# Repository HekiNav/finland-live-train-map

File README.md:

# Finland live train map

The project consist of the physical pcb and case as well as the server that processes the information from the api and serves it to the ESP-32 to process. The physical project is a pcb with LEDs marking the route for intercity trains across Finland. There are two versions of the map. A more simplified version with just the routes visible. Then there is the more geografically correct version with the borders of Finland printed on the silkscreen. The LEDs mark the position of trains in real time so you can see at a glance where the trains are. The case makes it possible to wall mount the pcb or have it on your desk.

This project was made for Hack Club [Fallout](https://fallout.hackclub.com) by [NoseFa](https://github.com/NoseFa) and [Hekinav](https://github.com/HekiNav).

## Repository structure / table of contents

NOTE! All software has been moved to [another repo (HekiNav/ltm-firmware)](https://github.com/HekiNav/ltm-firmware)

**Each directory contains its own README file with more detailed information on the specific section. Basic information is provided here.**

### [`/pcb`](./pcb/README.md)
Contains KiCad design files
View interactive PCB design in [KiCanvas](https://kicanvas.org/?github=https%3A%2F%2Fgithub.com%2FHekinav%2FFinland-Live-Train-Map%2Ftree%2Fmain%2Fpcb)

### [`/design`](./design/README.md)
Contains Map Design ideas and plans as Inkscape SVGs

### [`/server`](https://github.com/HekiNav/ltm-firmware/tree/main/server/README.md)
Contains the NodeJS server that processes data from Fintraffic to amore usable format

### [`/firmware`](https://github.com/HekiNav/ltm-firmware/tree/main/firmware/README.md)
Contains the Platformio firmware for the ESP32C3

### [BuildGuide.md](BuildGuide.md)
Contains instructions for building the project.

## Why this exists

This project was made because we wanted to work on something together and Hack Club was running the Fallout event. Hekinav has built a similar type of project before for Helsinki. [The Helsinki Live Train map](https://github.com/HekiNav/helsinki-live-train-map) and we decided that making one of all the Trains in Finland would be cool. This project is meant to be something to look at and something cool to have in your space. Thats why we put so much effort in the silkscreen of the pcb and the placement of the LED's. We wanted it to be good to look at.

## BOM

The BOM for this project is pretty much just making buying the PCB and then 3d printing the case (we are self-printing so we didn't add this). You can see the JLCPCB formatted [BOM.csv](./pcb/jlcpcb/production_files/BOM-fin-ltm.csv). We have some more detailed information about how to order it. Here is also a table that just includes the price of the PCB and the assembly, shipping + customs for it.

|         Part          |   Total price   |                     Link                            |   Extra info  | 
| --------------------- | --------------- | --------------------------------------------------- | ------------- |
| PCB                   |     14.83€      | [JLCPCB](https://jlcpcb.com/pcb-fabrication/fr4-pcb)|               |
| PCBA inc. components  |     136.03€     | [JLCPCB PCBA](https://jlcpcb.com/pcb-assembly)      | For specific component pricing see the JLCPCB bom in the pcb folder  |
| JLCPCB shipping       |     22.37€      | [Shipping](https://jlcpcb.com/shipping)             |               |
| Taxes / customs fees  |     44.18€      | [Tulli.fi](https://tulli.fi/tullilaskuri#/)         |               |
|                       |                 |                                                     |               |
| Total                 |     217.42€     |                                                     |               |

## Zine page

We were required to make a Zine page for Fallout. Available as a [`zine.pdf`](Zine.pdf)

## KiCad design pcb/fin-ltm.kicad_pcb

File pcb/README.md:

[Back to main page](https://github.com/HekiNav/finland-live-train-map/tree/main)
# PCB Design

- Made in KiCad with [CDFER's JLCPCB KiCad library](https://github.com/CDFER/JLCPCB-Kicad-Library).
- Inspiration for antenna and power system taken from [CDFER's live train maps](https://keastudios.co.nz). They are very cool!
- Designed to be fabricated and assembled by JLCPCB
    - PCBA by JLC because tiny components and hundreds of leds are hard to assemble manually. Also, LCSC components are very cheap with JLC.

## Main components

- ESP32-C3FH4 (chip)
    - 4MiB built-in flash
- Level Shifter (3V3 data from esp to 5V led data)
    - [TI SN74LV1T34DBVR](https://www.lcsc.com/product-detail/C100024.html)
- Power management
    - USB VBUS to 5V and 3V3 rails
    - Mosfet to shut down 5V rail
- 239 ARGB LEDs: [Xinglight XL-1615RGBC-2812B-S](https://www.lcsc.com/product-detail/C41413180.html)
    - The -S version is less bright and cheaper than the non -S version. 
    - These LEDs are a cheaper alternative (knockoff) to WorldSemi WS2812Bs

### KiCanvas viewer

View interactive PCB design in [KiCanvas](https://kicanvas.org/?github=https%3A%2F%2Fgithub.com%2FHekinav%2FFinland-Live-Train-Map%2Ftree%2Fmain%2Fpcb)

**NOTICE**: KiCanvas does not properly render everything, plase hide layers User.1-User.5 to view power circuitry

## Schematic

Some of the LEDs are missing because they were removed after making the initial layout

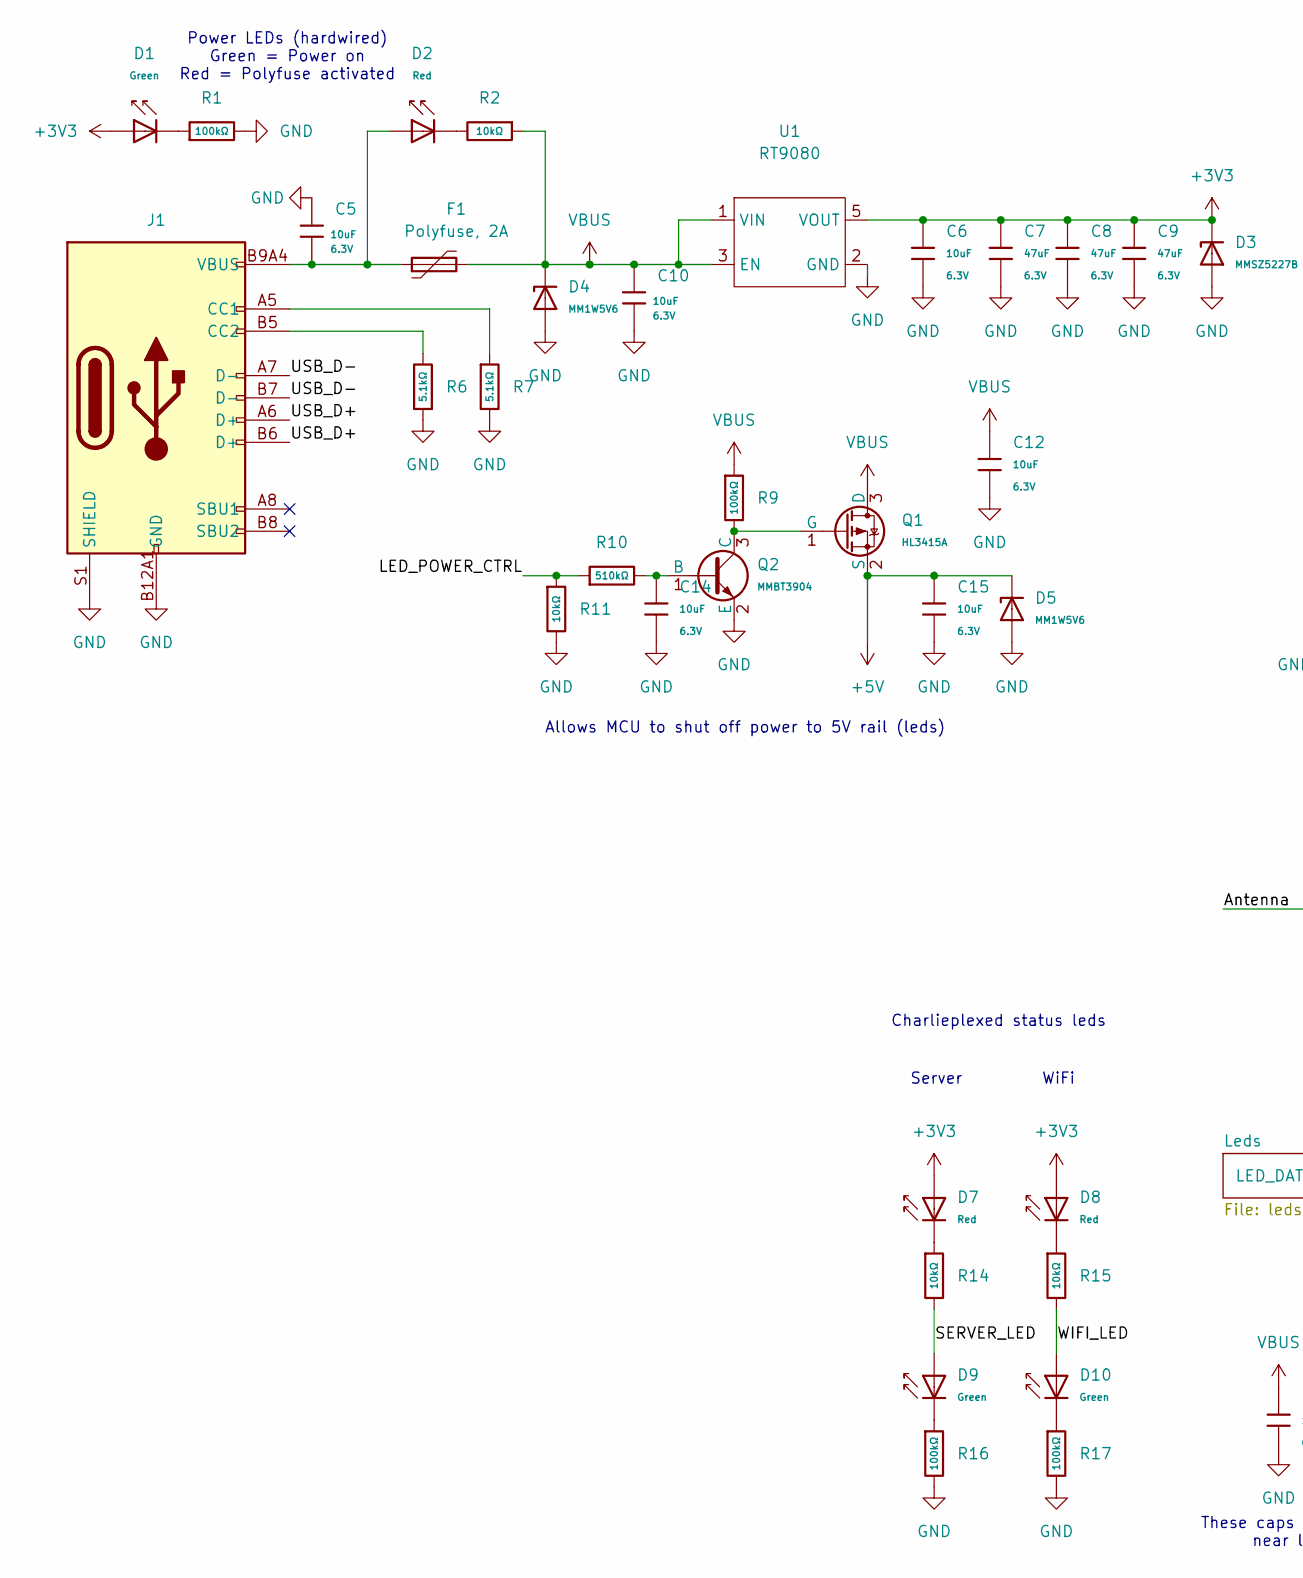
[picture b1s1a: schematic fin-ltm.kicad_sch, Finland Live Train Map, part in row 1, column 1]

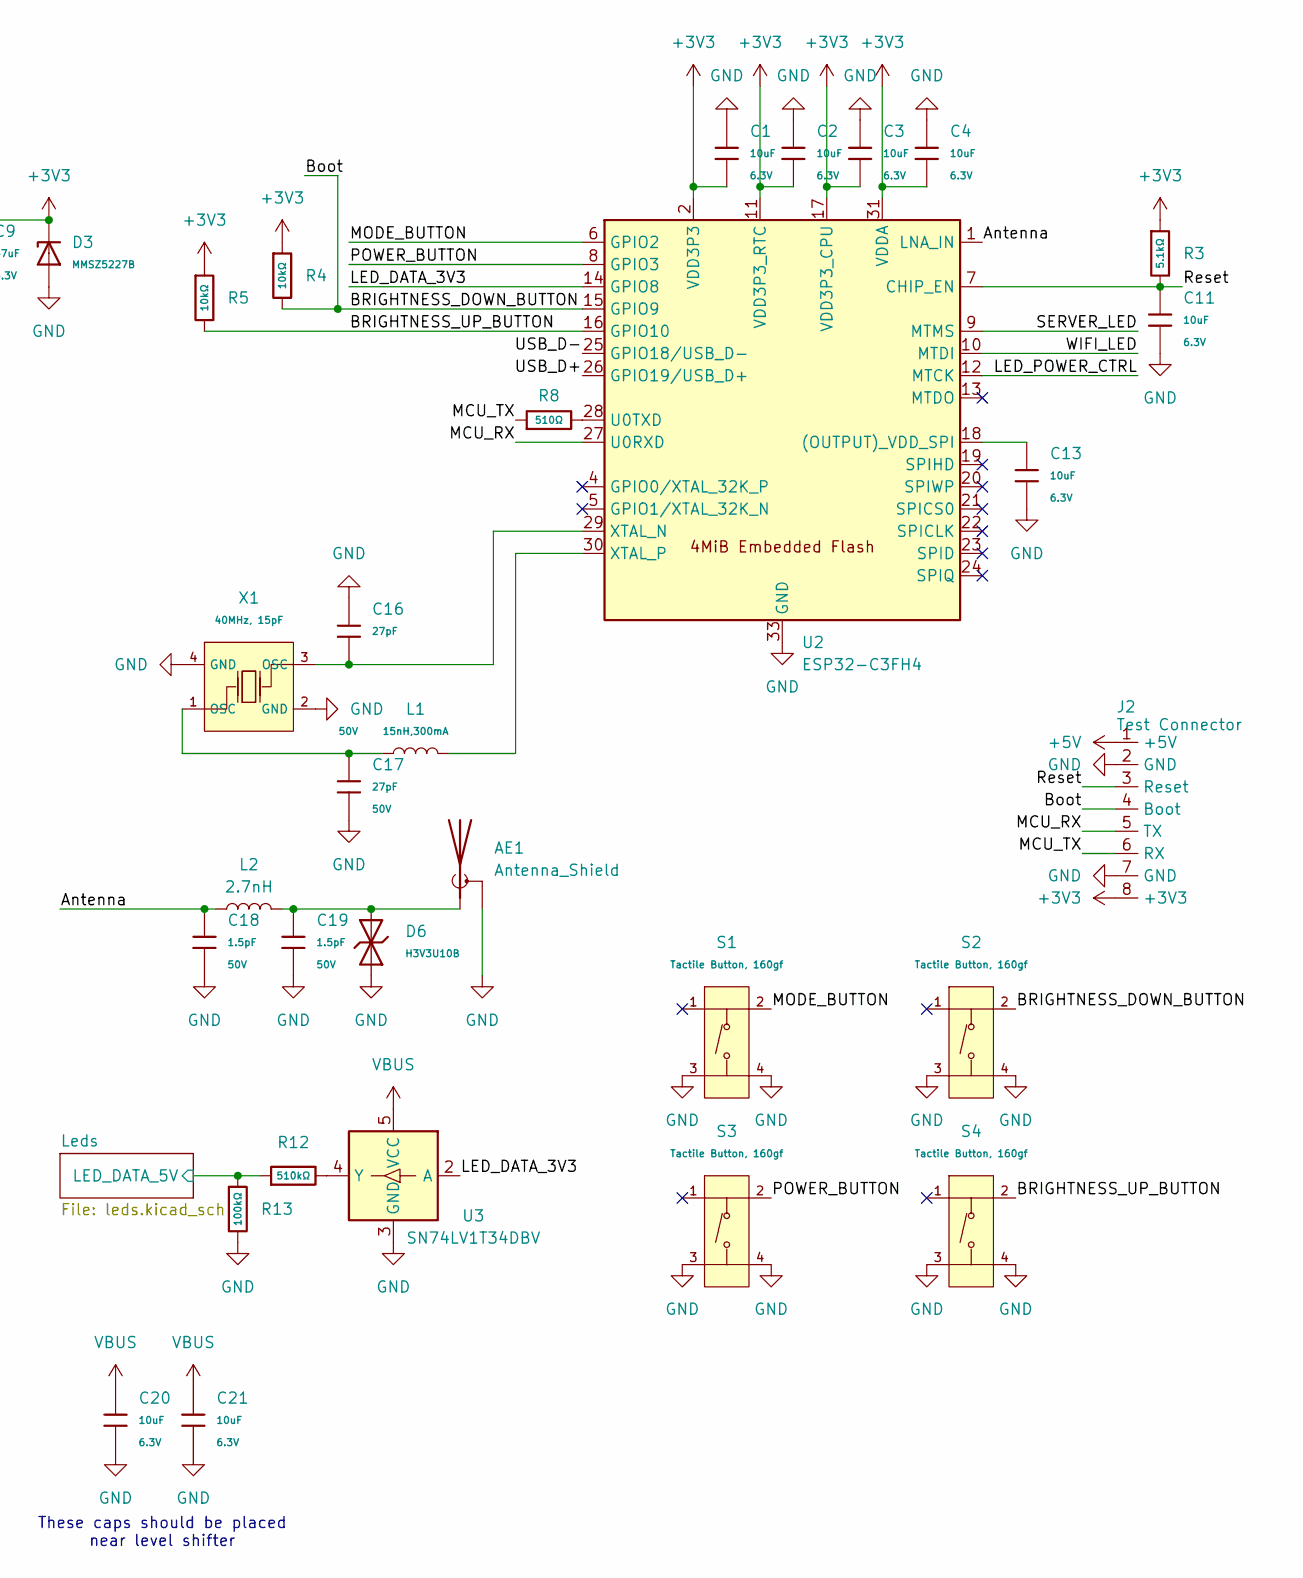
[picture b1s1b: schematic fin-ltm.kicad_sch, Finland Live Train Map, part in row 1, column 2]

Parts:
AE1: Antenna_Shield; Inverted_F_Antenna_2.4Ghz_1.0mmPCB_TI_CC2430DB.pretty
C1, C2, C3, C4, C5, C6, C10, C11, C12, C13, C14, C15, C20, C21: 10uF; C_0402; Voltage Rated 6.3V; Tolerance ±20%; Part CL05A106MQ5NUNC; LCSC C15525
C7, C8, C9: 47uF; C_0805; Voltage Rated 6.3V; Tolerance ±20%; Part CL21A476MQYNNNE; LCSC C16780
C16, C17: 27pF; C_0402; Voltage Rated 50V; Tolerance ±5%; Part 0402CG270J500NT; LCSC C1557
C18, C19: 1.5pF; C_0402; Voltage Rated 50V; Part 0402CG1R5C500NT; LCSC C1552
D1, D9, D10: Green; D_0805; Part KT-0805G; LCSC C2297
D2, D7, D8: Red; D_0805; Forward Voltage (VF) 1.6V~2.6V; Part NCD0805R1; LCSC C84256
D3: MMSZ5227B; D_SOD-123; Part MMSZ5227B; LCSC C22395553
D4, D5: MM1W5V6; D_SOD-123; Part MM1W5V6; LCSC C22435086
D6: H3V3U10B; D_DFN1006-2L; Part H3V3U10B; LCSC C20615782
F1: Polyfuse, 2A; Fuse_1206_3216Metric; LCSC C6165195
J1: Connector, USB-TYPE-C-16P; TYPE-C-SMD_HX-TYPE-C-16PIN; LCSC C2927039
J2: Test Connector; Test_connector
L1: 15nH,300mA; L_0402; Tolerance ±5%; Part SDCL1005C15NJTDF; LCSC C27143
L2: 2.7nH; L_0402; LCSC C77108
Q1: HL3415A; Q_SOT-23; Part HL3415A; LCSC C28646270
Q2: MMBT3904; Q_SOT-23; Part MMBT3904; LCSC C7420353
R1, R9, R13, R16, R17: 100kΩ; R_0402; Overload Voltage (Max) 50V; Tolerance ±1%; Part 0402WGF1003TCE; LCSC C25741
R2, R4, R5, R11, R14, R15: 10kΩ; R_0402; Overload Voltage (Max) 50V; Tolerance ±1%; Part 0402WGF1002TCE; LCSC C25744
R3, R6, R7: 5.1kΩ; R_0402; Overload Voltage (Max) 50V; Tolerance ±1%; Part 0402WGF5101TCE; LCSC C25905
R8: 510Ω; R_0402; Overload Voltage (Max) 50V; Tolerance ±1%; Part 0402WGF5100TCE; LCSC C25123
R10, R12: 510kΩ; R_0402; Overload Voltage (Max) 50V; Tolerance ±1%; Part 0402WGF5103TCE; LCSC C11616
S1, S2, S3, S4: Tactile Button, 160gf; SW-SMD_4P-L5.1-W5.1-P3.70-LS6.5-TL-2; Voltage Rating (Dc) 12V; Part TS-1187A-B-A-B; LCSC C318884
U1: RT9080; TSOT-23-5; LCSC C841192
U2: ESP32-C3FH4; QFN-32-1EP_5x5mm_P0.5mm_EP3.7x3.7mm_ThermalVias; LCSC C2858491
U3: SN74LV1T34DBV; SOT-23-5; LCSC C100024
X1: 40MHz, 15pF; OSC-SMD_4P-L3.2-W2.5-BL_SIT8008BI; PartID X322540MPB4SI; LCSC C9010

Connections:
+3V3: C1.2, C2.2, C3.2, C4.2, C6.1, C7.1, C8.1, C9.1, D1.2, D3.1, D7.2, D8.2, J2.8 (+3V3), R3.1, R4.1, R5.1, U1.5 (VOUT), U2.2 (VDD3P3), U2.3 (VDD3P3), U2.11 (VDD3P3_RTC), U2.17 (VDD3P3_CPU), U2.31 (VDDA), U2.32 (VDDA)
+5V: C15.1, D5.1, J2.1 (+5V), Q1.2 (S); also elsewhere on the board
/Antenna: C18.1, L2.1, U2.1 (LNA_IN)
/BRIGHTNESS_DOWN_BUTTON: J2.4 (Boot), R4.2, S2.2 (B), U2.15 (GPIO9)
/BRIGHTNESS_UP_BUTTON: R5.2, S4.2 (B), U2.16 (GPIO10)
/LED_DATA_3V3: U2.14 (GPIO8), U3.2 (A)
/LED_POWER_CTRL: R10.1, R11.1, U2.12 (MTCK)
/Leds/LED_DATA_5V: R12.1, R13.1; also elsewhere on the board
/MCU_RX: J2.5 (TX), U2.27 (U0RXD)
/MCU_TX: J2.6 (RX), R8.1
/MODE_BUTTON: S1.2 (B), U2.6 (GPIO2)
/POWER_BUTTON: S3.2 (B), U2.8 (GPIO3)
/Reset: C11.1, J2.3 (Reset), R3.2, U2.7 (CHIP_EN)
/SERVER_LED: D9.2, R14.2, U2.9 (MTMS)
/USB_D+: J1.A6 (D+), J1.B6 (D+), U2.26 (GPIO19/USB_D+)
/USB_D-: J1.A7 (D-), J1.B7 (D-), U2.25 (GPIO18/USB_D-)
/WIFI_LED: D10.2, R15.2, U2.10 (MTDI)
GND: AE1.2 (Shield), C1.1, C2.1, C3.1, C4.1, C5.1, C6.2, C7.2, C8.2, C9.2, C10.2, C11.2, C12.2, C13.2, C14.2, C15.2, C16.1, C17.2, C18.2, C19.2, C20.2, C21.2, D3.2, D4.2, D5.2, D6.1, J1.A12B1 (GND), J1.B12A1 (GND), J1.S1 (SHIELD), J2.2 (GND), J2.7 (GND), Q2.2 (E), R1.2, R6.1, R7.2, R11.2, R13.2, R16.2, R17.2, S1.3 (C), S1.4 (D), S2.3 (C), S2.4 (D), S3.3 (C), S3.4 (D), S4.3 (C), S4.4 (D), U1.2 (GND), U2.33 (GND), U3.3 (GND), X1.2 (GND), X1.4 (GND); also elsewhere on the board
unnamed: AE1.1 (A), C19.1, D6.2, L2.2
unnamed: C5.2, D2.2, F1.1, J1.A9B4 (VBUS), J1.B9A4 (VBUS)
unnamed: C17.1, L1.1, X1.1 (OSC)
unnamed: D1.1, R1.1
unnamed: D2.1, R2.2
unnamed: D7.1, R14.1
unnamed: D8.1, R15.1
unnamed: D9.1, R16.1
unnamed: D10.1, R17.1
unnamed: J1.A5 (CC1), R7.1
unnamed: J1.B5 (CC2), R6.2
unnamed: Q1.1 (G), Q2.3 (C), R9.2
unnamed: C14.1, Q2.1 (B), R10.2
unnamed: C13.1, U2.18 ((OUTPUT)_VDD_SPI)
unnamed: R8.2, U2.28 (U0TXD)
unnamed: C16.2, U2.29 (XTAL_N), X1.3 (OSC)
unnamed: L1.2, U2.30 (XTAL_P)
unnamed: R12.2, U3.4 (Y)
VBUS: C10.1, C12.1, C20.1, C21.1, D4.1, F1.2, Q1.3 (D), R2.1, R9.1, U1.1 (VIN), U1.3 (EN), U3.5 (VCC)

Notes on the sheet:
These caps should be placed near level shifter
Charlieplexed status leds
Allows MCU to shut off power to 5V rail (leds)
Power LEDs (hardwired) Green = Power on Red = Polyfuse activated
Server
WiFi
